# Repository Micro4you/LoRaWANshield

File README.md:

# RN2483shield

KiCad design for an Arduino compatible RN2483 (or RN2903) LoRaWAN shield.

Fork of the original [jpmeyers/RN2483shield](https://github.com/jpmeijers/RN2483shield).

Adjusted to:

 * use the Microchip specified RF trace geometry to maintain R&TTE (CE) and FCC testing compliance for the radio module (datasheet pg. 12),
 * ignore the 433MHz antenna trace (868MHz only),
 * use solder jumper connections for Serial UART connection,
 * normally connected jumpers for default connections:
   * Serial D3 Tx → Radio Serial Rx,
   * Serial D2 Rx → Radio Serial Tx,
 * Mosfet level converters on the UART connection to allow 5V→3.3V signal conversion,
 * Breakout of all GPIO pins on the radio (GPIO 0–13),
 * edge mounted SMA connetion for antenna.

## Required Parts

 * 1× Shield PCB,
 * 2× BSS138 SOT-23 N-channel MOSFET,
 * 5× 0603 10k resistors,
 * 1× SMA female edge jack,
 * 1× SMA 868MHz antenna,
 * 1× 1x10 stacking thru-headers,
 * 2× 1x8 stacking thru-headers,
 * 1× 1x6 stacking thru-headers

## Setting the Serial lines

By default, the Arduino D3 (Serial Tx) is connected to the Radio UART_RX, and the Arduino D2 (Serial Rx) is connected to the Radio UART_TX. By cutting between the pads marked by an asterisk in the Serial_TX and Serial_RX bank, these links can be severed, and a new connection made for each UART line by adding solder to bridge one pair of solder jumpers for each direction.

Only make connetions across one of each direction at a time to prevent multiplexing the digital pins on the Arduino, and don't connect both TX and RX to the same pin, as this will make communication very difficult!

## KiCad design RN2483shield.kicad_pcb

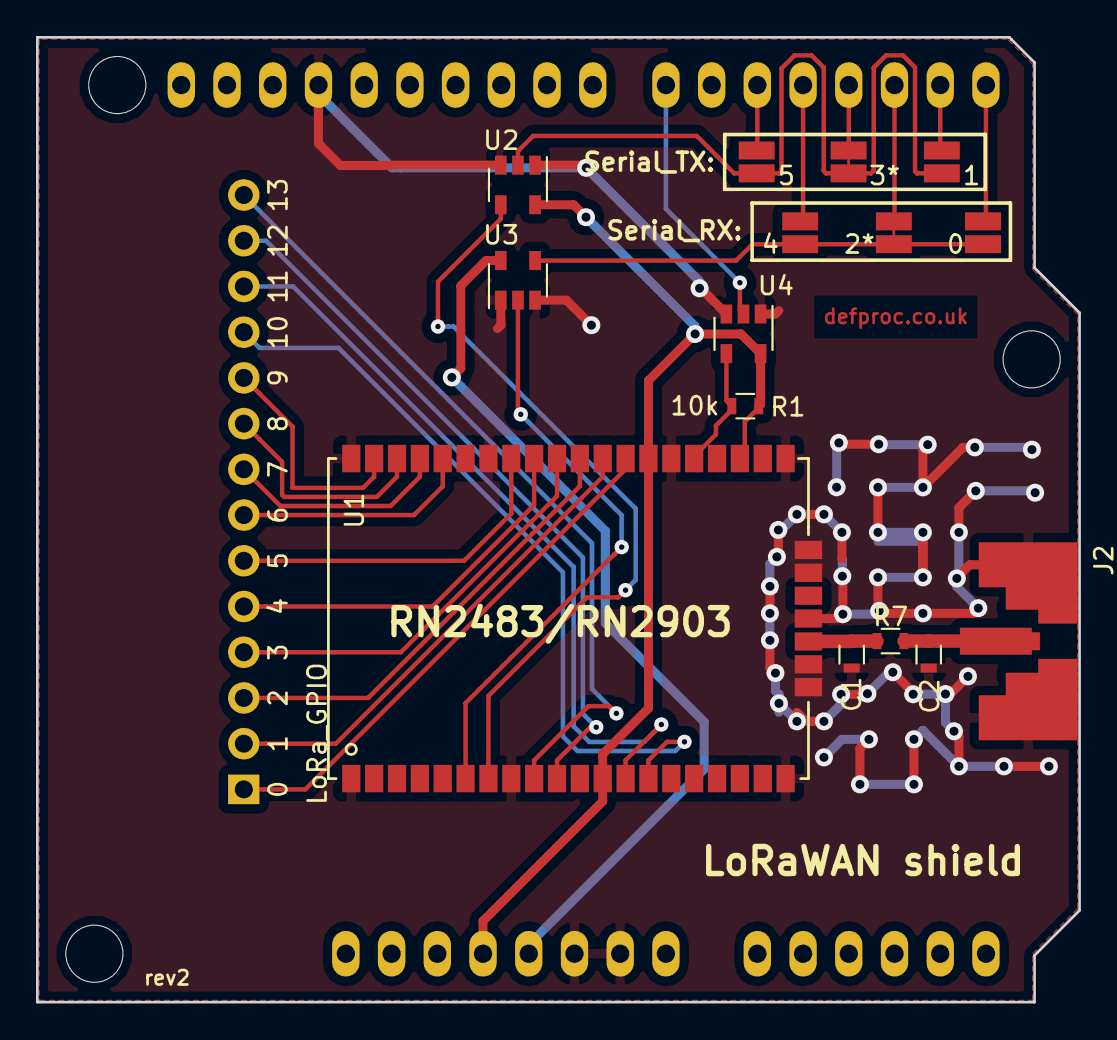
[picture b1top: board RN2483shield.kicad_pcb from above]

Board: 2 copper layers, 57.9 x 53.6 mm, 17 parts (0 on the bottom side), 31 nets.

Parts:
C1, C2: NC; R_0603
J1: LoRa_GPIO; CONN_1x14
J2: SMA_HF; multi-rf-sma-ufl
JP1, JP2, JP5, JP6: Jumper_NO_Small; NO_SMD_JPR
JP3, JP4: Jumper_NC_Small; NC_SMD_JPR
R1: 10k; R_0603
R7: 0R; R_0603
SHIELD1: ARDUINO_SHIELD; ARDUINO_SHIELD_NOICSP
U1: RN2483/RN2903; RN2483
U2, U3, U4: SN74LVC1G125; SOT-23-5

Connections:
+3V3: R1.2, SHIELD1.3V3, U1.12, U1.34, U2.5, U4.5
+5V: SHIELD1.5V, U3.5
D0: JP1.2, SHIELD1.0
D1: JP2.2, SHIELD1.1
D2_RX: JP3.2, SHIELD1.2
D3_TX: JP4.2, SHIELD1.3
D4: JP5.2, SHIELD1.4
D5: JP6.2, SHIELD1.5
D7: SHIELD1.7, U4.2
GND: C1.2, C2.2, J2.2, SHIELD1.GND1, SHIELD1.GND2, SHIELD1.GND3, U1.1, U1.8, U1.11, U1.20, U1.21, U1.22, U1.24, U1.26, U1.27, U1.28, U1.33, U1.41, U1.47, U2.1, U2.3, U3.1, U3.3, U4.1, U4.3
GPIO_0: J1.1, U1.35
GPIO_1: J1.2, U1.36
GPIO_2: J1.3, U1.37
GPIO_3: J1.4, U1.38
GPIO_4: J1.5, U1.39
GPIO_5: J1.6, U1.40
GPIO_6: J1.7, U1.43
GPIO_7: J1.8, U1.44
GPIO_8: J1.9, U1.45
GPIO_9: J1.10, U1.46
GPIO_10: J1.11, U1.14
GPIO_11: J1.12, U1.13
GPIO_12: J1.13, U1.10
GPIO_13: J1.14, U1.9
unnamed: C1.1, R7.2, U1.23
unnamed: C2.1, J2.1, R7.1
unnamed: JP1.1, JP5.1, U3.4
unnamed: JP2.1, JP4.1, JP6.1, U2.2
unnamed: R1.1, U1.32, U4.4
RX_RADIO: U1.7, U2.4
TX_RADIO: U1.6, U3.2

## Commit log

2017-06-05 redraft of shield
2017-06-05 redrafted the board with edgeSMA, gpio breakouts and solderpad serial connections
2017-06-05 and with title, link, revision and makers mark
2017-06-05 and remove the soldermask from the solder jumpers
2017-06-05 removed freetronics libraries
2017-06-05 and a more detail on the changes
2017-06-06 removed sheet ref from gerbers and included board renders
2018-01-23 EOD: redrafted board with new level shifters
